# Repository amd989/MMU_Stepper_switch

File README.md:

# MMU Stepper Switch

Recreated this circuit with through-hole components

Ready to order JLCPCB gerber attached.

Tested and working with Marlin Firmware.

EasyEDA PCB layout (new)

## BOM

| No. | Quantity | Comment | Designator | Manufacturer Part | Supplier Part | Supplier |
|-----|----------|---------|------------|-------------------|---------------|----------|
| 1 | 1 | 10uF | C1 | UKL1E100KDDANA | C1580057 | LCSC |
| 2 | 1 | 100nF | C2 | CC1E104ZA1FD3F5O10MF | C254077 | LCSC |
| 3 | 3 | L240CTZ0G3MM | D1,D2,D3 | L240CTZ0G3MM | C9900093286 | LCSC |
| 4 | 5 | XH2.54-4P | E0,E1,E2,E3,E-IN | xh2.54-4p | C9900015350 | LCSC |
| 5 | 1 | ZX-XH2.54-5PZZ | P1 | ZX-XH2.54-5PZZ | C7429635 | LCSC |
| 6 | 2 | IRF520NPBF_C709596 | Q1,Q2 | IRF520NPBF-VB | C709596 | LCSC |
| 7 | 3 | 470Ω | R1,R4,R7 | MFR-25JT-52-470R | C176518 | LCSC |
| 8 | 2 | 68Ω | R2,R5 | MFR-25JT-52-68R | C176538 | LCSC |
| 9 | 2 | 10kΩ | R3,R6 | MFR-25JT-52-10K | C176451 | LCSC |
| 10 | 3 | GM-RELAY-R40-V12 | RL1,RL2,RL3 | | | |

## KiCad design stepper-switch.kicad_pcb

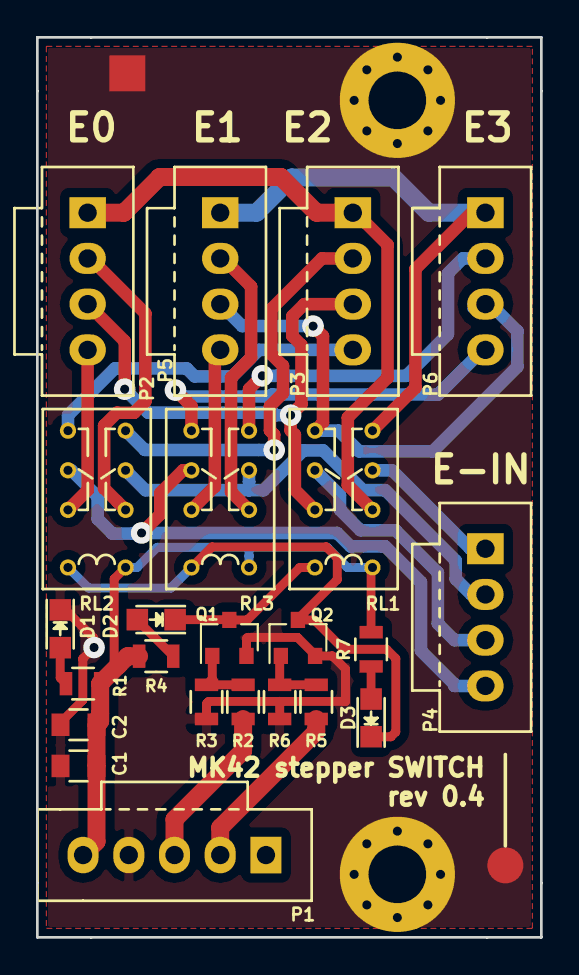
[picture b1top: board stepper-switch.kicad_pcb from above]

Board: 2 copper layers, 28.0 x 50.0 mm, 23 parts (0 on the bottom side), 27 nets.

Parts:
C1: 10u; C_0805
C2: 100n; C_0805
D1, D2, D3: LED; LED_0805
P1: MOLEX 70543-0004; Pin_1x05-XL
P2, P3, P4, P5, P6: MOLEX 70543-0003; Pin_1x04-XL
Q1, Q2: MMBF170LT1G; SOT-23
R1, R4, R7: 470R; R_0805
R2, R5: 68R; R_0805
R3, R6: 10k; R_0805
RL1, RL2, RL3: Realy-AZ850; Rel_TE_CONNECTIVITY_1-1462038-3

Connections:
+5V: C1.1, C2.1, P1.5, R1.1, R4.1, R7.1, RL1.1, RL2.1, RL3.1
GND: C1.2, C2.2, D1.1, P1.4, Q1.2, Q2.2, R3.2, R6.2
unnamed: D1.2, R1.2
unnamed: D2.1, Q1.3, RL1.10
unnamed: D2.2, R4.2
unnamed: D3.1, Q2.3, RL2.10, RL3.10
unnamed: D3.2, R7.2
unnamed: P1.2, R5.2
unnamed: P1.3, R2.2
unnamed: P2.1, P3.1, RL1.2
unnamed: P2.2, RL2.2
unnamed: P2.3, P3.3, RL1.9
unnamed: P2.4, RL2.9
unnamed: P3.2, RL2.4
unnamed: P3.4, RL2.7
unnamed: P4.1, RL1.3
unnamed: P4.2, RL2.3, RL3.3
unnamed: P4.3, RL1.8
unnamed: P4.4, RL2.8, RL3.8
unnamed: P5.1, P6.1, RL1.4
unnamed: P5.2, RL3.2
unnamed: P5.3, P6.3, RL1.7
unnamed: P5.4, RL3.9
unnamed: P6.2, RL3.4
unnamed: P6.4, RL3.7
unnamed: Q1.1, R2.1, R3.1
unnamed: Q2.1, R5.1, R6.1

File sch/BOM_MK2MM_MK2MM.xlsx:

No. | Quantity | Comment | Designator | Manufacturer Part | Supplier Part | Supplier
1 | 1 | 10uF | C1 | UKL1E100KDDANA | C1580057 | LCSC
2 | 1 | 100nF | C2 | CC1E104ZA1FD3F5O10MF | C254077 | LCSC
3 | 3 | L240CTZ0G3MM | D1,D2,D3 | L240CTZ0G3MM | C9900093286 | LCSC
4 | 5 | XH2.54-4P | E0,E1,E2,E3,E-IN | xh2.54-4p | C9900015350 | LCSC
5 | 1 | ZX-XH2.54-5PZZ | P1 | ZX-XH2.54-5PZZ | C7429635 | LCSC
6 | 2 | IRF520NPBF_C709596 | Q1,Q2 | IRF520NPBF-VB | C709596 | LCSC
7 | 3 | 470Ω | R1,R4,R7 | MFR-25JT-52-470R | C176518 | LCSC
8 | 2 | 68Ω | R2,R5 | MFR-25JT-52-68R | C176538 | LCSC
9 | 2 | 10kΩ | R3,R6 | MFR-25JT-52-10K | C176451 | LCSC
10 | 3 | GM-RELAY-R40-V12 | RL1,RL2,RL3

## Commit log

2026-03-18 feat: ✨ support through-hole components.
2026-03-18 docs: 📝 update readme.md
2026-03-19 style: 🎨 reorganize the repo
